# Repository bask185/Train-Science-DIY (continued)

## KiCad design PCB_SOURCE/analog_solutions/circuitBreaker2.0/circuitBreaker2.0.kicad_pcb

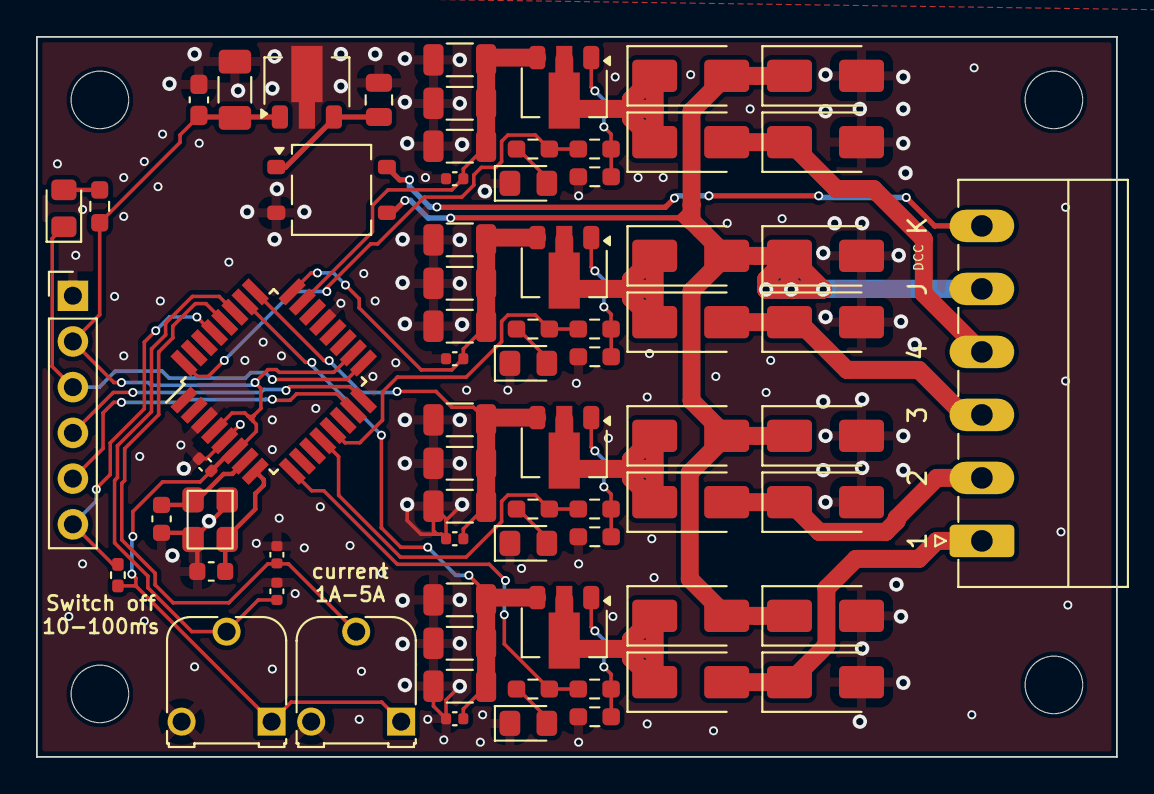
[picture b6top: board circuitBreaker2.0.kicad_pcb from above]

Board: 2 copper layers, 60.0 x 40.0 mm, 71 parts (0 on the bottom side), 38 nets.

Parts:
C201, C203: 12pF; C_0603_1608Metric
C202, C401, C501, C601, C701, C901, C902: 100nF; C_0402_1005Metric
C301: 470nF; C_0805_2012Metric
C302: 100nF; C_0603_1608Metric_Pad1.08x0.95mm_HandSolder
C303: 100uF; C_1206_3216Metric_Pad1.33x1.80mm_HandSolder
D201, D401, D501, D601, D701: LED; LED_0805_2012Metric_Pad1.15x1.40mm_HandSolder
D301: MB10S; TO-269AA
D402, D403, D404, D405, D502, D503, D504, D505, D602, D603, D604, D605, D702, D703, D704, D705: D; D_SMA
J202: ICSP; PinHeader_1x06_P2.54mm_Vertical
J801: Screw_Terminal_01x06; PhoenixContact_MC_1,5_6-G-3.5_1x06_P3.50mm_Horizontal
Q401, Q501, Q601, Q701: TM10N06SI; SOT-89-3
R201: 6k2; R_0603_1608Metric_Pad0.98x0.95mm_HandSolder
R202: 10k; R_0402_1005Metric_Pad0.72x0.64mm_HandSolder
R401, R501, R601, R701: 680R; R_0603_smalltext
R402, R502, R602, R702: 22R; R_0603_smalltext
R403, R503, R603, R703: 10k; R_0603_smalltext
R404, R405, R406, R504, R505, R506, R604, R605, R606, R704, R705, R706: 0R1; R_1206_3216Metric
RV901, RV902: R_Potentiometer; Potentiometer_Runtron_RM-065_Vertical
U202: ATmega328-A; TQFP-32_7x7mm_P0.8mm
U301: L78L05_SOT89; SOT-89-3
Y201: Crystal_GND2; crystal_arduino

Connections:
+5V: C202.1, C302.1, C303.1, J202.2, R201.1, R202.1, RV901.1, RV902.1, U202.4 (VCC), U202.6 (VCC), U202.18 (AVCC), U301.1 (OUT)
/POWER/J: D301.3, D402.2 (A), D403.1 (K), D502.2 (A), D503.1 (K), D602.2 (A), D603.1 (K), D702.2 (A), D703.1 (K), J801.5
/POWER/K: D301.4, J801.6
/channel1/CS: C401.1, Q401.3 (S), R404.2, R405.1, R406.1, U202.23 (PC0)
/channel1/ENABLE: R401.1, R402.1, U202.32 (PD2)
/channel1/OUT: D404.2 (A), D405.1 (K), J801.4
/channel2/CS: C501.1, Q501.3 (S), R504.2, R505.1, R506.1, U202.24 (PC1)
/channel2/ENABLE: R501.1, R502.1, U202.13 (PB1)
/channel2/OUT: D504.2 (A), D505.1 (K), J801.3
/channel3/CS: C601.1, Q601.3 (S), R604.2, R605.1, R606.1, U202.25 (PC2)
/channel3/ENABLE: R601.1, R602.1, U202.12 (PB0)
/channel3/OUT: D604.2 (A), D605.1 (K), J801.2
/channel4/CS: C701.1, Q701.3 (S), R704.2, R705.1, R706.1, U202.26 (PC3)
/channel4/ENABLE: R701.1, R702.1, U202.9 (PD5)
/channel4/OUT: D704.2 (A), D705.1 (K), J801.1
/potentiometer/current: C902.1, RV902.2, U202.28 (PC5)
/potentiometer/time: C901.1, RV901.2, U202.27 (PC4)
/uProcessor/LED: D201.1 (K), J202.3, U202.17 (PB5)
/uProcessor/MISO: J202.4, U202.16 (PB4)
/uProcessor/MOSI: J202.5, U202.15 (PB3)
/uProcessor/Reset: J202.6, R202.2, U202.29 (~RESET/PC6)
/uProcessor/X1: C201.2, U202.7 (XTAL1/PB6), Y201.1
/uProcessor/X2: C203.2, U202.8 (XTAL2/PB7), Y201.3
GND: C201.1, C202.2, C203.1, C301.2, C302.2, C303.2, C401.2, C501.2, C601.2, C701.2, C901.2, C902.2, D301.2 (-), D401.1 (K), D403.2 (A), D405.2 (A), D501.1 (K), D503.2 (A), D505.2 (A), D601.1 (K), D603.2 (A), D605.2 (A), D701.1 (K), D703.2 (A), D705.2 (A), J202.1, R403.1, R404.1, R405.2, R406.2, R503.1, R504.1, R505.2, R506.2, R603.1, R604.1, R605.2, R606.2, R703.1, R704.1, R705.2, R706.2, RV901.3, RV902.3, U202.3 (GND), U202.5 (GND), U202.21 (GND), U301.2 (GND), Y201.2 (GND), Y201.4 (GND)
unnamed: D201.2 (A), R201.2
unnamed: D401.2 (A), R401.2
unnamed: D402.1 (K), D404.1 (K), Q401.2 (D)
unnamed: D501.2 (A), R501.2
unnamed: D502.1 (K), D504.1 (K), Q501.2 (D)
unnamed: D601.2 (A), R601.2
unnamed: D602.1 (K), D604.1 (K), Q601.2 (D)
unnamed: D701.2 (A), R701.2
unnamed: D702.1 (K), D704.1 (K), Q701.2 (D)
unnamed: Q401.1 (G), R402.2, R403.2
unnamed: Q501.1 (G), R502.2, R503.2
unnamed: Q601.1 (G), R602.2, R603.2
unnamed: Q701.1 (G), R702.2, R703.2
VCC: C301.1, D301.1 (+), U301.3 (IN)

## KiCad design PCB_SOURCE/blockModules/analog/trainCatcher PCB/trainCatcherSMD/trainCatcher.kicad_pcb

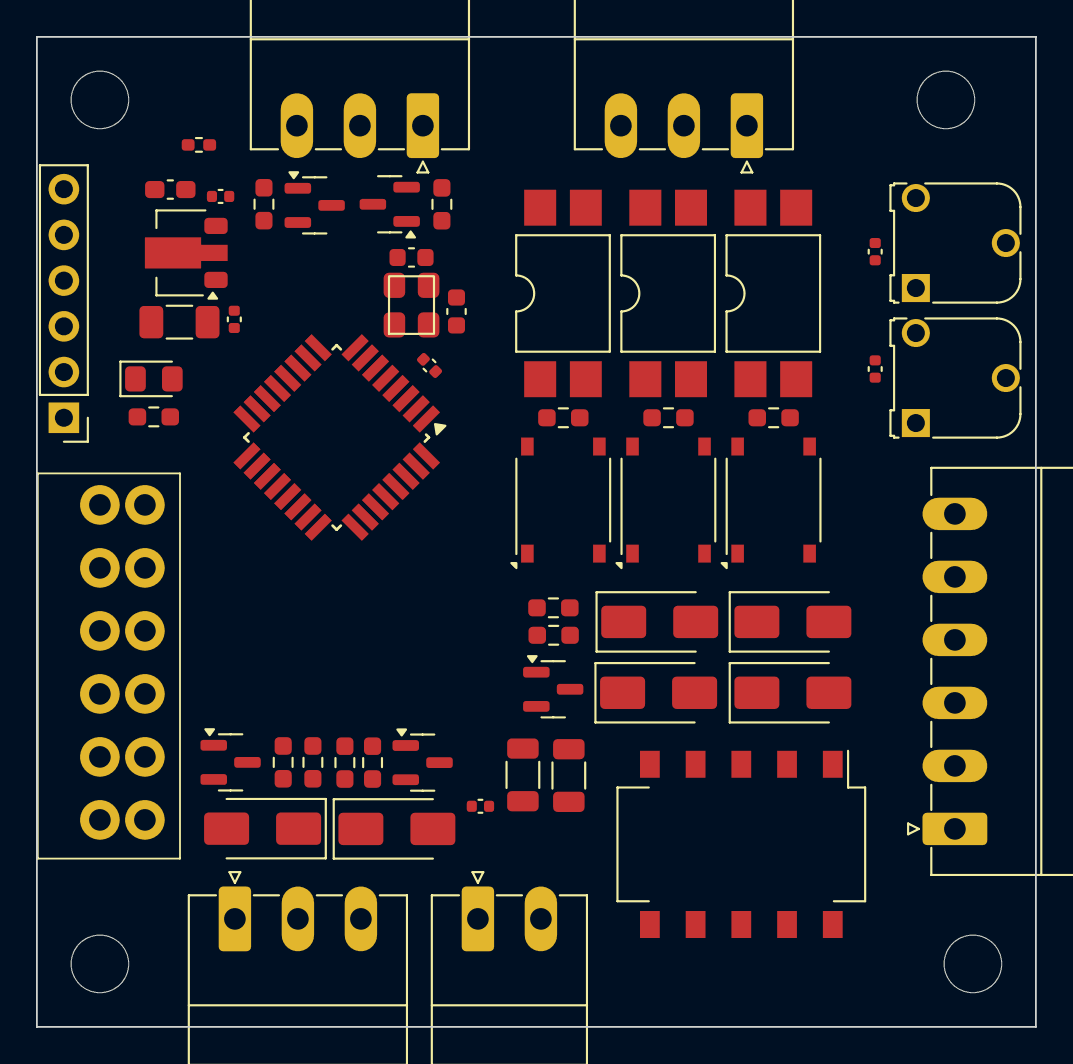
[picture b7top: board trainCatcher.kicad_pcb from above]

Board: 2 copper layers, 55.5 x 55.0 mm, 56 parts (0 on the bottom side), 44 nets, no tracks yet.

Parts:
C1, C202, C301, C701, C901, C1201: 100nF; C_0402_1005Metric
C201: 330nF; C_0603_1608Metric_Pad1.08x0.95mm_HandSolder
C203: 100uF; C_1206_3216Metric_Pad1.33x1.80mm_HandSolder
C302, C303: 12pF; C_0603_1608Metric
D2, D3, D4: 2A bridge; Diode_Bridge_Diotec_ABS
D5, D6, D8, D10, D1201, D1401: SS53; D_SMA
D301: LED; LED_0805_2012Metric_Pad1.15x1.40mm_HandSolder
J3: Screw_Terminal_01x02; PhoenixContact_MC_1,5_2-G-3.5_1x02_P3.50mm_Horizontal
J301: ICSP; PinHeader_1x06_P2.54mm_Vertical
J601, J1401, J1601: Screw_Terminal_01x03; PhoenixContact_MC_1,5_3-G-3.5_1x03_P3.50mm_Horizontal
J1101: Conn_01x06_Pin; connector_3.50mm_6P horizontal_MALE
J1301: Conn_01x06_Socket; PhoenixContact_MC_1,5_6-G-3.5_1x06_P3.50mm_Horizontal
Q3, Q1201, Q1401: AO3400A; SOT-23
Q4, Q1601: NPN_TOR; SOT-23
R3, R4, R5: 47R; R_0603_smalltext
R8, R1203: 0R1; R_1206_3216Metric
R12, R1202, R1402: 22k; R_0603_smalltext
R13, R1201, R1401: 22R; R_0603_smalltext
R15, R1601: 1k5; R_0603_smalltext
R301: 6k2; R_0603_1608Metric_Pad0.98x0.95mm_HandSolder
R302: 10k; R_0402_1005Metric_Pad0.72x0.64mm_HandSolder
RV701, RV901: 10k; Potentiometer_Runtron_RM-065_Vertical
SW1501: SW_DIP_x06; SW_DIP_SPSTx05_Slide_Omron_A6S-510x_W8.9mm_P2.54mm
U26, U27, U28: EL814; SMDIP-4_W9.53mm
U201: L78L05_SOT89; SOT-89-3
U301: ATmega328-A; TQFP-32_7x7mm_P0.8mm
Y301: Crystal_GND2; crystal_arduino

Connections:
+5V: C202.1, C203.1, C301.1, J301.2, R301.1, R302.1, RV701.1, RV901.1, U201.1 (OUT), U301.4 (VCC), U301.6 (VCC), U301.18 (AVCC)
+18V: C1.1, C201.1, D10.1 (K), D1401.1 (K), J1101.5, J1301.5, J1401.2, J1601.1, U201.3 (IN)
/PWM/COM: D2.3, D3.3, D4.3, D5.2 (A), D6.1 (K), U26.2, U27.2, U28.2
/PWM/CS: C1201.1, Q1201.2 (S), R8.1, R1203.1, U301.28 (PC5)
/PWM/PWM: R1201.1, U301.12 (PB0)
/atmega/LED: D301.1 (K), J301.3, U301.17 (PB5)
/atmega/MISO: J301.4, U301.16 (PB4)
/atmega/MOSI: J3.2, J301.5, U301.15 (PB3)
/atmega/Reset: J301.6, R302.2, U301.29 (~RESET/PC6)
/atmega/Rx: J1301.2, U301.1 (PD3)
/atmega/Tx: J1101.2, U301.32 (PD2)
/atmega/X1: C302.2, U301.7 (XTAL1/PB6), Y301.1
/atmega/X2: C303.2, U301.8 (XTAL2/PB7), Y301.3
/atmega/brakeSpeed: C901.1, RV901.2, U301.19 (ADC6)
/atmega/brake_sensor: U26.4, U301.10 (PD6)
/atmega/buf_sensor: U28.4, U301.11 (PD7)
/atmega/pauseTime: C701.1, RV701.2, U301.22 (ADC7)
/atmega/point0: R13.2, U301.30 (PD0)
/atmega/point1: R1401.1, U301.31 (PD1)
/atmega/signal1: R15.1, U301.13 (PB1)
/atmega/stop_sensor: U27.4, U301.9 (PD5)
/brake/TRACK: D2.4, J601.2, R3.1
/stop/TRACK: D3.4, J601.3, R4.1
BUFFER: D4.4, J1101.1, J1301.1, R5.1
GND: C1.2, C201.2, C202.2, C203.2, C301.2, C302.1, C303.1, C701.2, C901.2, C1201.2, D6.2 (A), D8.2 (A), J3.1, J301.1, J1101.6, J1301.6, Q3.2 (S), Q4.2 (E), Q1401.2 (S), Q1601.2 (E), R8.2, R12.2, R1202.2, R1203.2, R1402.2, RV701.3, RV901.3, SW1501.6, SW1501.7, SW1501.8, SW1501.9, SW1501.10, U26.3, U27.3, U28.3, U201.2 (GND), U301.3 (GND), U301.5 (GND), U301.21 (GND), Y301.2 (GND), Y301.4 (GND)
unnamed: D2.1 (+), D2.2 (-)
unnamed: D3.1 (+), D3.2 (-)
unnamed: D4.1 (+), D4.2 (-)
unnamed: D10.2 (A), J1401.3, Q3.3 (D)
unnamed: D301.2 (A), R301.2
unnamed: D5.1 (K), D1201.1 (K), Q1201.3 (D)
unnamed: D1401.2 (A), J1401.1, Q1401.3 (D)
unnamed: J1601.2, Q4.3 (C)
unnamed: J1601.3, Q1601.3 (C)
unnamed: Q3.1 (G), R12.1, R13.1
unnamed: Q4.1 (B), R1601.2
unnamed: Q1201.1 (G), R1201.2, R1202.1
unnamed: Q1401.1 (G), R1401.2, R1402.1
unnamed: Q1601.1 (B), R15.2
unnamed: R3.2, U26.1
unnamed: R4.2, U27.1
unnamed: R5.2, U28.1
ring_L: J601.1, J1101.3, J1301.3
ring_R: D8.1 (K), D1201.2 (A), J1101.4, J1301.4

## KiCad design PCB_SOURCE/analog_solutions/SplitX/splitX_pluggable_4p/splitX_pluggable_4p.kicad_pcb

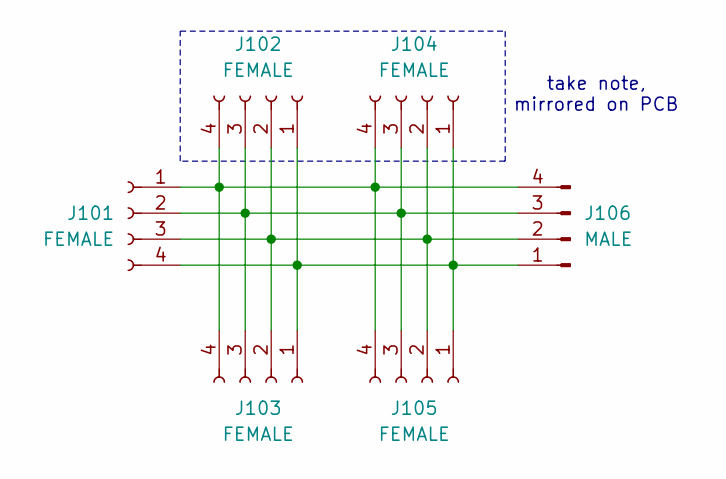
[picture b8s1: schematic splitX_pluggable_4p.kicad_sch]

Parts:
J101, J102, J103, J104, J105: FEMALE; PhoenixContact_MC_1,5_4-G-3.5_1x04_P3.50mm_Horizontal
J106: MALE; connector_3.50mm_4P horizontal_MALE

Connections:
unnamed: J101.1, J102.4, J103.4, J104.4, J105.4, J106.4
unnamed: J101.2, J102.3, J103.3, J104.3, J105.3, J106.3
unnamed: J101.3, J102.2, J103.2, J104.2, J105.2, J106.2
unnamed: J101.4, J102.1, J103.1, J104.1, J105.1, J106.1

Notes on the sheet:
take note, mirrored on PCB

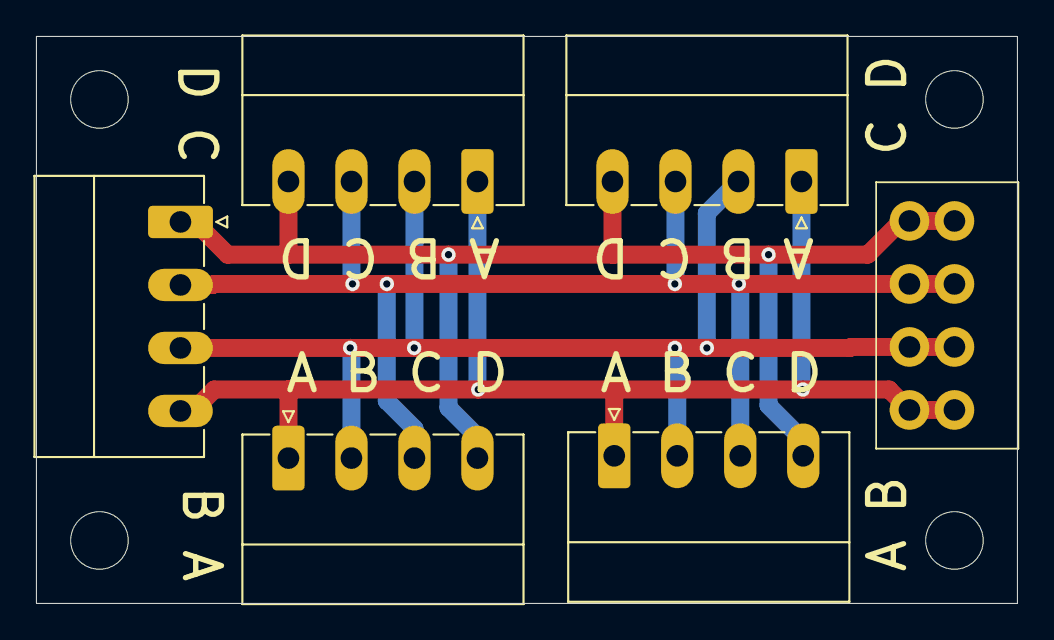
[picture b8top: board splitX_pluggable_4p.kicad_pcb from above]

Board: 2 copper layers, 54.5 x 31.5 mm, 6 parts (0 on the bottom side), 4 nets.

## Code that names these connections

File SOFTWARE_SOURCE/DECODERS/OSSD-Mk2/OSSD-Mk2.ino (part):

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    uint16          dccExt :  1 ; 
    uint16   locoFunctions :  2 ; // enable the usage of locomotive function. this can be 1 address with 16 functions or 4 addresses with 4 functions
    uint16   maxCduVoltage : 12 ;
    uint16          hasCdu :  1 ; // needed? or autodetect? In essence with constant power supply, the software should ever switch.
    uint16          rcn213 :  1 ; // address offset for multimaus icw old roco boosters. Addresses are to be substracted with 4 when option is OFF.
    // I used double addresses so any system can turn on or off this setting. Address 1001 and 997 both turn it ON
    // addresses 1000 and 996 turn it OFF.
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
    loadCoils() ;
    
    dcc.pin( 2, 0 ) ;
    dcc.init( MAN_ID_DIY, 11, FLAGS_OUTPUT_ADDRESS_MODE | FLAGS_DCC_ACCESSORY_DECODER, 0 );
}

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    //         rightLed.setEventBleeps(5) ;            // go flash LED's
    //         leftLed.setEventBleeps(5) ;

    //         runMode = 0 ;                       // set lockout time of atleast 5 seconds.
    //         lockoutTime = millis() ;
    //     }
    // }
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    uint8_t  bitOffset       = 0 ;
    uint8_t  maxFunctions    = squashAddresses() ;      // check settings of all coils and determen how many addresses that are in use.
    uint16_t dccBaseAddress  = coil[0].getAddress() ;   // the address of the first coil determens to which loco address to listen to.
    uint8_t  neededAddresses = 1 ;                      // used for the Lok maus support. As we have 4 dcc addresses per loco address, we need more loco addresses per decoder 

    if( settings.locoFunctions == FANTASTIC_FOUR )      // lok maus support, F1-F4 of sequential loco addresses are used to control a decoder 
    {
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
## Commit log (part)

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2023-03-07 fixed minor bug of panel Mk I
2023-03-19 made a mistake with nummering of one side
2023-03-19 also changed the PCB of splitX 2
2023-03-23 added turning loop module. still need to add the suplementing IR sluice
2023-03-23 added sharps IR sluice to repo
2023-04-20 altered turning loop with good relay footprint, larger capacitor footprint and flywheel diode
2023-04-20 added gerber file to project
2023-04-20 added BOM for turning loop as well
2023-04-26 added servo driver w DCC interface to repo (not yet operational) and I updated the geber and bom of the turning loop module. New order should be placed
2023-04-30 made new turning loop pcb with an extra transistor to invert the signal
2023-05-01 Added panelX Mk III code. Buttons now work via NX style. One must customize the route array in order to get this to work
2023-05-12 added the mosfet driver to this repository
2023-05-12 added remaining splits and breakout boards
2023-05-12 Added DCC nano power shield and the current sensor's PRO file
2023-05-27 PanelX MkI has been upgraded with loconet. I may need to check the licenses
2023-05-31 enhanced the panelX Mk1 with loconet
2023-06-06 created the layout manager. It is a revised version of the older multimaushancer/robomaus projects.
    This version makes use of an arduino UNO as well as LCD shield. It is mentioned as a DIY project. I will order a couple of prototypes though.
2023-06-07 added layoutManager source code. Most code is already filled in. Basic program control buttons and sensors should work
2023-06-07 filled in some blanks and added some comments in how to fill in the LCD space. Most things should work as is now
2023-06-07 added calculated reference values to read in the switches
2023-06-08 added some code to keep track of which functions of which addresses are changed. More work is needed to display the functions on the LCD.
    I may want to revisit the option to use a for-loop somehow
2023-06-08 added for loop to determen which function is set/cleared. Lcd functions are in place, it may even work at this time
2023-06-08 minor bug fix and added some comments
2023-06-14 Added the LoPiTs-XS project. It is an absolute minimalistic DCC decoder for driving only
2023-06-27 added Lopits source as well as new PWM contoller
2023-06-28 added a tasks.json
2023-06-28 removed tasks.json
2023-06-29 altered the Lnet interface PCB with silk texts
2023-06-29 removed XpressNet added state machine to handle shuttle service build in detection of potentiometers. added potentiometer for max speed added potentiometer for acceleration added potentiometer for wa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
2023-06-29 should have functional shuttle service. Take note it is untested
2023-06-29 minor refacotring action
2023-07-03 added a minimum speed option. I still need to let the acceleration control lockout the deadzone created by the min speed
2023-07-03 added bullhead sleeper along with gerbers
2023-07-03 pwm controller has been partially debugged. Potentiometer seems to work. Only the lockout of lower speeds hasn't been implemented yet.
    The detection of potentiometers also seems to work well.
2023-07-03 lockout min speed seems to work. Also found a good default accel setting of 15ms
2023-07-04 added text file with github subfolder download link added AHOB code
2023-07-04 heavily refactored code. Untested. Should work tho... Added Fader.cpp/.h to fade in and fade out LEDs
2023-07-05 added missing 2 servo's and fixed a small bug. Code remains untested
2023-07-05 changed blink time values and added comments. Code for DCC is needed Code for DFmini mp3 player is needed
2023-07-05 Added the open source coil driver
2023-07-06 finalized routing on the Open source solenoid decoder
2023-07-06 added 2 new PCB designs
2023-07-06 some dcc decoder work done. screw terminals need some spacing so I get 4 groups of 6 terminals. I need solder pads underneath the rectifier for the event it dies or more current is needed.
2023-07-06 added yed graph file for configuring
2023-07-10 added missing files. Mostly OSSD stuff
2023-07-11 added lots of signal code. Project is not compilable at this time. Code should be debugged using serial terminal
2023-07-12 project made compilable. Initial tests are underway
2023-07-12 merge
2023-07-12 Changed a lot the signal code. Code is not compile-able at this time. I need the signal control part to work with the different signal types. Still lots of work
2023-07-13 big commit. The Signal class itself came a far way. Every object can succesfully determen which IO pins and which dcc addresses he should use.
    Setting the signals has not yet been tested. Also the actual LED updating is not done yet.
2023-07-13 Added some code to handle coils and constant outputs. It may be a fruitfull idea to let the constant outputs act as a signal with 2 aspects and 1 output. This is perfectly viable.
    The coils are somewhat trickier to do so.
    I want to update the config button with a debouncer. It makes the state machine easier
2023-07-13 single outputs are now treated as 2 aspect signal with 1 output
2023-07-13 added some comments. I tested the single outputs (seems to work with pins and addresses) added the ability for a single output to blink
2023-07-14 Changed code complete to not use a separate coil drive class. This has been moved to the signal class. Untested, compilable
2023-07-17 Added railway crossings to signal.cpp. I do need some differenting between the blinking lights.
2023-07-17 added many signals to array
2023-07-18 code is made compilable again. Progmem should work. but it must be tested. also added 2 belgian home signals
2023-07-18 blinking LED works well corresponding to mode. Test routine is used
2023-07-18 Program seems to work to do list has been adjusted new signal PCB project added, not finished
2023-07-18 much of the signal PCB is ready for now. Mouse bites are needed but I still lack Austrian and Swiss signals
2023-07-18 commit for the night. Added missing DCC files for lopits-xs
2023-07-19 changed some signal boards
2023-07-19 added signal type spreadsheet
2023-07-19 changed much of signal pcb tester
2023-07-19 Most code works. DCC is verified. Several output modes are tested. The one thing that does not yet work is the config menu. getSignalType is run prematurely
2023-07-19 changed some index numbers in the signal list
2023-07-20 added spread sheets for signal aspect images also swapped the LED connections in the Signal.cpp. They ordered in normal order from left to right
2023-07-20 added PDF file as well (also hosted by wordpress). Signals documentation is reasonally okay. I do want to improve the explanation about objects/signals
2023-07-20 There is a minor bug with which a point was set too often due to repeating DCC signals It has now been 'solved' with a 500ms lockout. But this could results is ignored DCC packets
2023-07-21 points are tested and seem to work well
2023-07-22 added swiss L main and distant signals. They are untested. Documentation not yet done
2023-07-22 Added french signals as well, untested. Documentation not yet done
2023-07-22 added images for swiss signals, to be added to pdf. pdf not up to date yet.
2023-07-24 updated comment
2023-07-24 added ledstrip and tracksplitter
2023-07-24 re done PCB for led strip. Only the Lm317 lacks LSCS number, otherwise it looks good
2023-07-24 minor tweaks. added signal connections.ods
    Documentation is up to date with software
2023-07-25 re-organized the entire folder structure and added a readme.md for github. May want to add a readme.txt as well
2023-08-01 changed build script according to new binary path. Added new functionality to use unique DCC addresses per signal. You can turn it on with address 4 in config and with 3 you can turn it off Untested 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
    It may be desirable to remove the blinking aspect of a single output. It may disrupt expected addresses..
    Potential EEPROM bug not yet found. Should verivy integrity of upload process. It should not make a difference but still..
2023-08-01 changed the state machine so that a short button press can also be used to set unique addresses, if enabled you do need to pick an index first. The blinking LED should be clear in the matter.
    Also the states of picking a signal type or selecting a unique address will fall back to getIndex instead of idle.
    This allow you to configure the decoder faster. Pressing the button while not in idle, will abort any action.
    Also swapped the 8th and 9th german signals and double red and red + shunt was swapped to correspond with documentation.
    Website needs altering
    Added state machine in yEd to match the code. And I updated the flow chart, though it may be revised for clarity's sake.
2023-08-02 fixed some small bugs. German signal position has been corrected. And if unique addresses is anabled you can also adjust signal type again. outputs are cleared to 0 upon booting/factory reset signal 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
2023-08-03 commit 4 merge
2023-08-03 added relay manager to project.
2023-08-03 fixed big in OSSD
2023-08-03 made some changed to relay manager
2023-08-10 added Xnet Block Unit project
2023-08-14 routed Xnet block unit. Ready for SMT assembly
2023-08-14 added production files to xnet block unit
2023-09-03 many changes. Going to get some missing projects back
2023-09-03 Added missing files
2023-09-26 added OS servo driver
2023-09-26 added schematics to incorporate company name
2023-09-26 added production files
2023-10-04 added missing things.
2023-10-05 changed 4mm sleeper layout and made gerbers
2023-10-30 commit 4 push
2023-10-31 added missing S88 files to repo
2023-11-29 Changed OSSD code to retain aspects in EEPROM. In the event that the power has been cut-off. The OSSD can resume it's last known state. This is untested and I may want to change this into an option.
2024-01-08 added many files including S88 project and modifcations to servo driver project
2024-02-24 massive overhaul of folder structure and added release folder for SW and HW
2024-03-21 many changes
2024-04-23 added some board files and Xnet block unit binary
2024-04-26 added and modified servo driver code
2024-05-14 added servo driver and S88 image
2024-07-05 added some files
2024-07-22 added god knows how many files
2024-07-29 added the latching relay
2024-07-31 Changed all 4 LED strips with 500R potentiometer and warm white 0805 LEDS Also put production files in RELEASE folder
2024-09-04 Added public licences to all of train-science DIY code. I do need to strip this from NMRA library though
2024-09-04 shoud have corrected all DCC, Loconet and Xnet licences now
2024-09-23 Added PDF files for all schematics
2024-09-23 added copy of Loconet current sense feedback to DIY repo for redesign
2024-10-13 Organized entire Open Source Line of products
2024-11-07 adjusted OS-ServoDriver Mk2 to power on servo's upo booting. This ensures that they are in the last known positions
2024-11-10 Updated servoDriver Mk2 software. It contains a fix for a nasy eeprom bug, caused by the nmra DCC library. All servo's are also set to their last known position upon booting.
2024-11-10 added jpg for the 19cm led strip
2024-11-10 changed BOM and CPL for OSSD due to stock amount issues for screw ternminals
2024-11-10 updated release folder with new BOM and CPL for OSSD
2024-11-13 added missing upload files for servo decoders
2024-11-23 added LED strip schematic in academy folder
2024-12-02 added some boards, new turning loop module with sleeper, all eating LED as well as servoDecoderInEnclosure
2024-12-19 added S88 current sense to releases and update OSSD decoder
2024-12-24 Added s88 current sense version, and changed turning loop module THT
2024-12-24 removed some unneeded files
2024-12-24 updated schematic PDF
2025-01-31 added some files, but mainly this is to update hex file of OSSD
2025-02-01 added analog control panel stuff
2025-02-24 added some PCB designs
2025-03-05 added missing files. working on ossd mk2 code
2025-05-20 added single light decoder
2025-06-13 renamed some projects and organized the relays
2025-06-13 deleted files I dont want
2025-07-09 upgraded servo driver code to newest standard
2026-05-20 fixed bug in ahob program among others
